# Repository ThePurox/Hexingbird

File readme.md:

# Hexingbird
Hexingbird is a [hummingbird](https://github.com/PJE66/hummingbird) style split 30 key keyboard designed around [hexagonal keycaps](https://hw.s-ol.nu/HEX-keycaps/), which require Choc v1 switches.
It uses the CH552T controller and [FAK firmware](https://github.com/semickolon/fak).

The electronic design is inspired by the [MIAO MCU board](https://github.com/kilipan/miao) and adapted for split operation.

# BOM
| Part             | LCSC-Part Nr | amount |
|------------------|--------------|--------|
| USB-C            | C223907      | 4      |
| CH552T           | C111367      | 2      |
| BAV70 Diodes     | C727123      | 18     |
| USBLC6-2SC6      | C6807798     | 2      |
| PMEG2010EA       | C193668      | 2      |
| Push buttons     | C115357      | 4      |
| Fuse             | C311055      | 2      |
| 5.1k-Resistor    | C23186       | 4      |
| 10k-Resistor     | C25804       | 2      |
| 1uF-Capacitor    | C2991434     | 4      |
| Hot-Swap-Sockets |              | 30     |
| Choc V1 Switches |              | 30     |

# Buildguide
Before we start let's get our coordinates clear.
The PCB is reversible, but not symmetric when flipped.
You can see this for example with the USB-jack; it's contacts for soldering are only on one side.
I will refer to this side as right top `RT`.
The top side of the right half (`RT`) is equivalent to the bottom side of the left half `LB`.
And vice versa the top side of the left half `LT` is equivalent to the bottom side of right half `RB`.

## Right half
Start with soldering the right half of the keyboard.
This side is easier, as all components (except for the hot-swap sockets) are soldered to the same side, i.e. `RT`.
I advise using a hotplate or hot air to solder the MCU and the USB-jack.
If you are experienced with hand soldering feel free to solder them by hand.
Three components require you to pay attention to the orientation of the component, i.e. the `CH552T`, `USBLC6-2SC6` and `PMEG2010EA`, the latter two are diodes for the ESD-protection.
For the `CH552T` and `USBLC6-2SC6` there are white lines on the PCB, with one line being slightly longer than the other. The side with the extended line is marks the corner in which the dot/dimple of the IC has to be placed.

The next components to solder are the USB-jacks.
After you have successfully soldered the electric pins of the USB-jack, make sure to also solder the metal legs on the side, as they will give stability to the jack.

Now you have completed the hard part, treat yourself with some pads on the shoulder, before we continue with the small two terminal components.
Next to the `CH552T` you will find four pads, these are for the two capacitors.
Next to the top USB-jack you see spots for four components, from top right to bottom left these are the fuse, `PMEG2010EA`-Schottky diode, and two 5.1k Resistors.
The orientation of the diode is important.
The white line on its housing has to face away from the USB-jack.
Another way of orientating the diode is to look closely on the solder-pads of the diode.
One of the pads is shaped like an arrow.
The arrow points towards the white line of the diode.
For the other components the orientation does not matter.

Next solder in the `RESET` and `BOOT` push buttons, as well as the 10k resistor between them.
Finally  install the `BAV70` diodes.

Congratulations, you have now soldered in all the necessary electronic components, you can now flash the firmware (see below) for the central half on this half and test, whether all keys work. All keys except the tucky thumb should work. The tucky thumb requires a bodge wire to function. Will we add the bodge wire, after soldering the hot-swap sockets.

The solder pads above and below the USB-jacks, as well as the pads next to the bottom USB-jack are supposed to be left empty.

## Left half
The left half is a bit more tricky to solder than the right half, as the MCU and the USB-jacks are soldered to different sides of the PCB.
If you are not careful while soldering, the components on the other side might fall off the PCB, or shift around. You don't want either to happen.
One trick to work around this annoyance, is to solder the `CH552T` and `USBLC6-2SC6` to `LT` first, then solder the USB-jacks to `LB`. When soldering the USB-jacks, only put the USB-jack part of the PCB on your hotplate.
If you heat up to much of the PCB, the MCU will fall off the board.

With the USB-jacks, the `CH552T` and the `USBLC6-2SC6` in place, you have completed the hardest part of soldering this keyboard.
From here on it is smooth sailing.
Next solder the `BAV70` diodes to `LB`.
Solder in all the remaining passive components to `LT` just as with the right half.

You can now test the left half by flashing the peripheral firmware onto it, connecting the two keyboard halves with through the USB-jacks with a bird next to them.

After you have confirmed, that all keys except for the tucky thumbs work, it is time to solder in the hot-swap sockets to the bottom sides of the two halves, i.e. the sides without the MCU.

If you are one of the lucky people that got a PCB at Mechanicon 2024 you have to add a bodge wire as shown in the picture, to each half:

# Flashing the firmware
This keyboard is designed for the [FAK-firmware](https://github.com/semickolon/fak).
I've provided some example configuration files in [my fork](https://github.com/ThePurox/fak-config) of the fak-config repository with the keyboard name `hexingbird`.

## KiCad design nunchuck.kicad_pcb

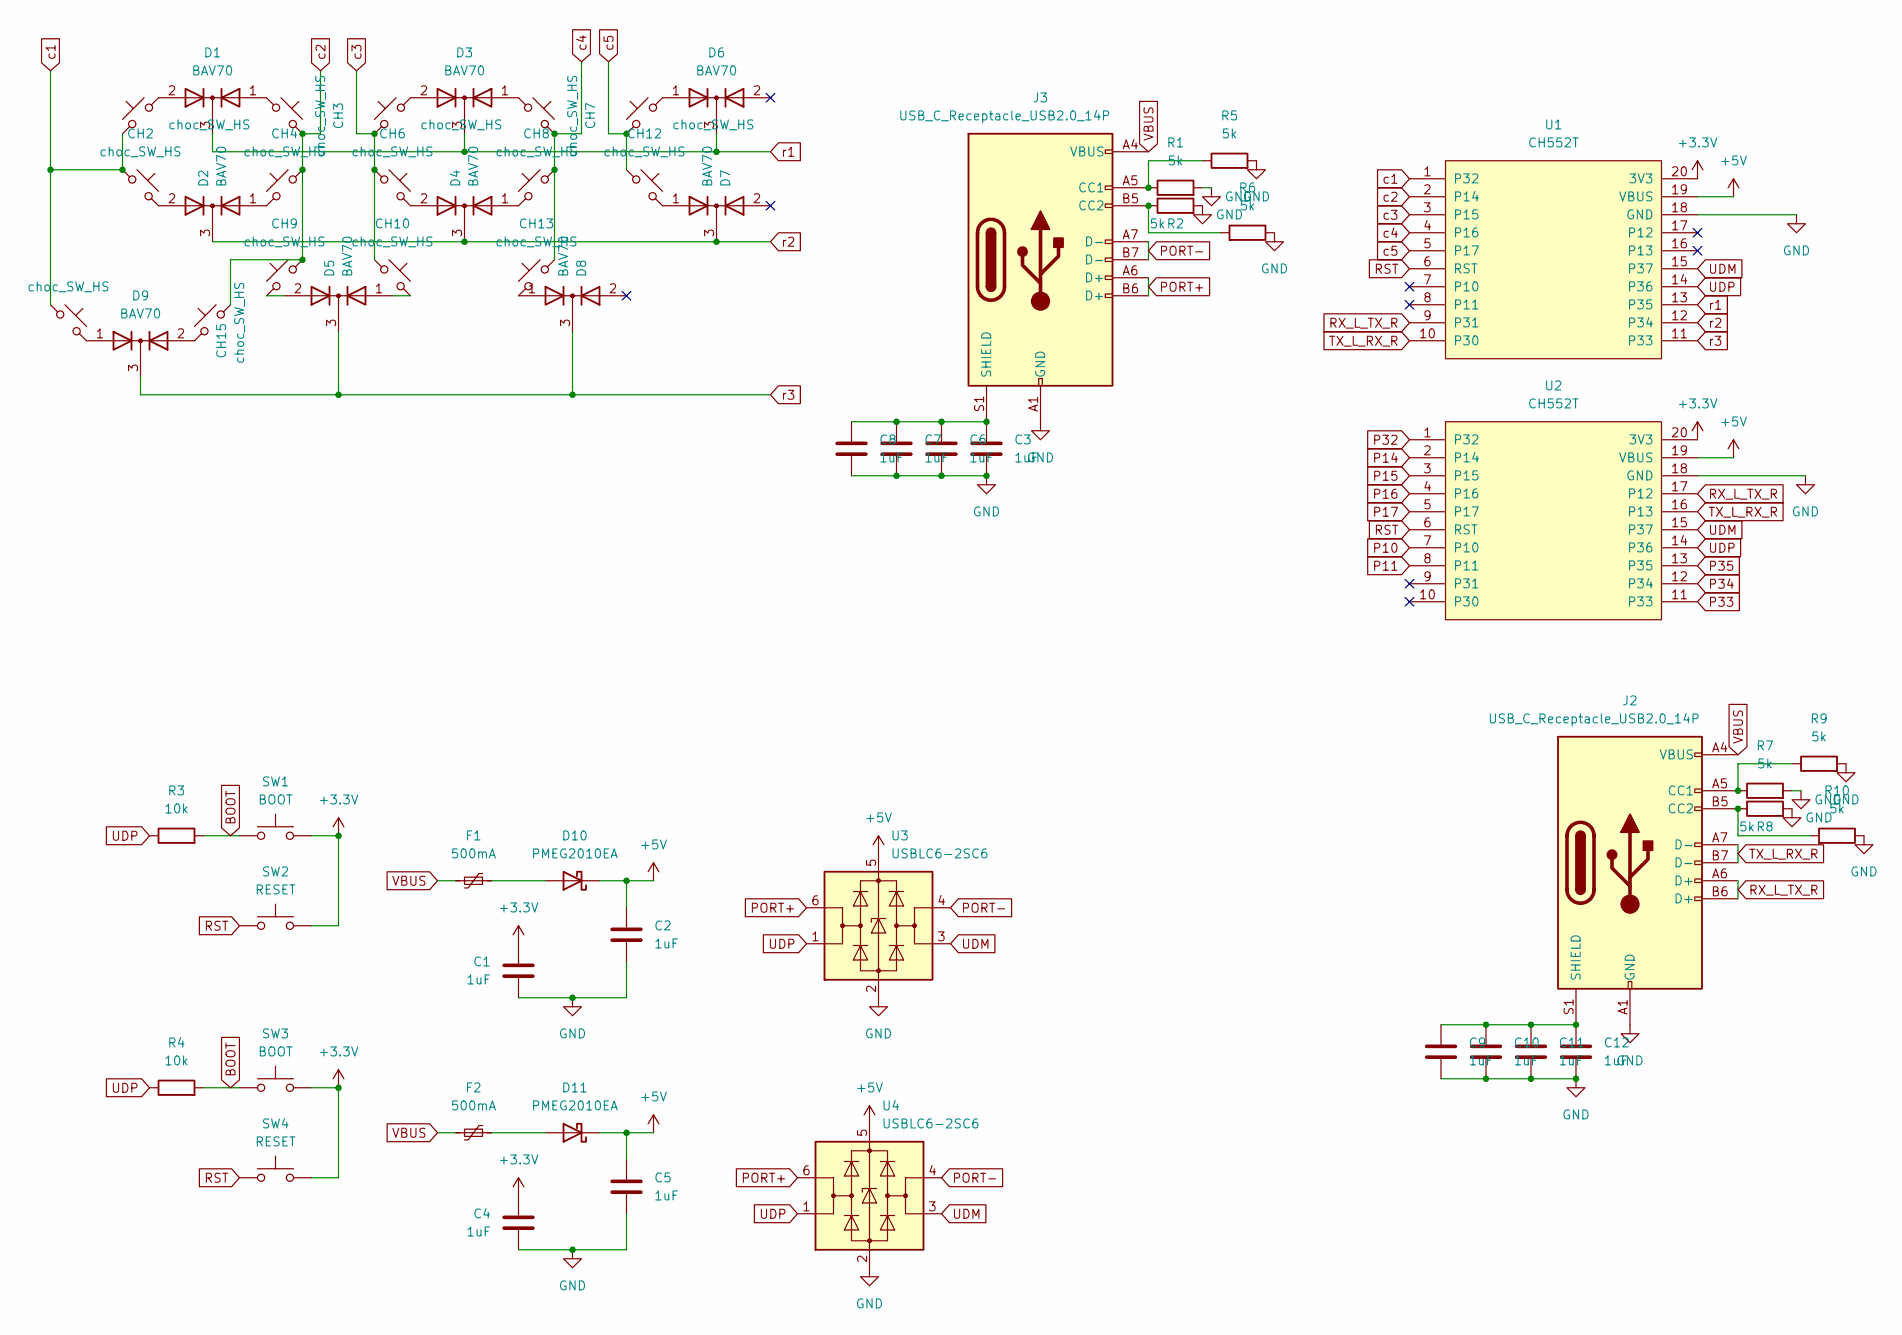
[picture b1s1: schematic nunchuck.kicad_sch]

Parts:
C1, C2, C3, C4, C5, C6, C7, C8, C9, C10, C11, C12: 1uF; C_0603_1608Metric_Pad1.08x0.95mm_HandSolder
CH1, CH2, CH3, CH4, CH5, CH6, CH7, CH8, CH9, CH10, CH11, CH12, CH13, CH14, CH15: choc_SW_HS; PG1350_hotswap_reversible
D1, D2, D3, D4, D5, D6, D7, D8, D9: BAV70; SOT-23
D10, D11: PMEG2010EA; D_SOD-323_HandSoldering
F1, F2: 500mA; Fuse_0603_1608Metric_Pad1.05x0.95mm_HandSolder
J2, J3: USB_C_Receptacle_USB2.0_14P; USB_C_Receptacle_HRO_TYPE-C-31-M-14
R1, R2, R5, R6, R7, R8, R9, R10: 5k; R_0603_1608Metric_Pad0.98x0.95mm_HandSolder
R3, R4: 10k; R_0603_1608Metric_Pad0.98x0.95mm_HandSolder
SW1, SW3: BOOT; SW_Push_SPST_NO_Alps_SKRK
SW2, SW4: RESET; SW_Push_SPST_NO_Alps_SKRK
U1, U2: CH552T; TSSOP-20_4.4x6.5mm_P0.65mm; LCSC C111367
U3, U4: USBLC6-2SC6; SOT-23-6

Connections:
+3.3V: C1.1, C4.1, SW1.2, SW2.2, SW3.2, SW4.2, U1.20 (3V3), U2.20 (3V3)
+5V: C2.1, C5.1, D10.1 (K), D11.1 (K), U1.19 (VBUS), U2.19 (VBUS), U3.5 (VBUS), U4.5 (VBUS)
BOOT: R3.2, R4.2, SW1.1, SW3.1
GND: C1.2, C2.2, C3.2, C4.2, C5.2, C6.2, C7.2, C8.2, C9.2, C10.2, C11.2, C12.2, J2.A1 (GND), J2.A12 (GND), J2.B1 (GND), J2.B12 (GND), J3.A1 (GND), J3.A12 (GND), J3.B1 (GND), J3.B12 (GND), R1.2, R2.2, R5.2, R6.1, R7.2, R8.2, R9.2, R10.1, U1.18 (GND), U2.18 (GND), U3.2 (GND), U4.2 (GND)
unnamed: CH1.2, D1.2 (A)
unnamed: CH2.2, D2.2 (A)
unnamed: CH3.2, D1.1 (A)
unnamed: CH4.2, D2.1 (A)
unnamed: CH5.2, D3.2 (A)
unnamed: CH6.2, D4.2 (A)
unnamed: CH7.2, D3.1 (A)
unnamed: CH8.2, D4.1 (A)
unnamed: CH9.2, D5.2 (A)
unnamed: CH10.2, D5.1 (A)
unnamed: CH11.2, D6.1 (A)
unnamed: CH12.2, D7.1 (A)
unnamed: CH13.2, D8.1 (A)
unnamed: CH14.2, D9.1 (A)
unnamed: CH15.2, D9.2 (A)
unnamed: D10.2 (A), F1.1
unnamed: D11.2 (A), F2.1
unnamed: J2.A5 (CC1), R7.1, R9.1
unnamed: J2.B5 (CC2), R8.1, R10.2
unnamed: C9.1, C10.1, C11.1, C12.1, J2.S1 (SHIELD)
unnamed: J3.A5 (CC1), R1.1, R5.1
unnamed: J3.B5 (CC2), R2.1, R6.2
unnamed: C3.1, C6.1, C7.1, C8.1, J3.S1 (SHIELD)
P10: U2.7 (P10)
P11: U2.8 (P11)
P14: U2.2 (P14)
P15: U2.3 (P15)
P16: U2.4 (P16)
P17: U2.5 (P17)
P32: U2.1 (P32)
P33: U2.11 (P33)
P34: U2.12 (P34)
P35: U2.13 (P35)
PORT+: J3.A6 (D+), J3.B6 (D+), U3.6 (I/O1), U4.6 (I/O1)
PORT-: J3.A7 (D-), J3.B7 (D-), U3.4 (I/O2), U4.4 (I/O2)
RST: SW2.1, SW4.1, U1.6 (RST), U2.6 (RST)
RX_L_TX_R: J2.A6 (D+), J2.B6 (D+), U1.9 (P31), U2.17 (P12)
TX_L_RX_R: J2.A7 (D-), J2.B7 (D-), U1.10 (P30), U2.16 (P13)
UDM: U1.15 (P37), U2.15 (P37), U3.3 (I/O2), U4.3 (I/O2)
UDP: R3.1, R4.1, U1.14 (P36), U2.14 (P36), U3.1 (I/O1), U4.1 (I/O1)
VBUS: F1.2, F2.2, J2.A4 (VBUS), J2.A9 (VBUS), J2.B4 (VBUS), J2.B9 (VBUS), J3.A4 (VBUS), J3.A9 (VBUS), J3.B4 (VBUS), J3.B9 (VBUS)
c1: CH1.1, CH2.1, CH14.1, U1.1 (P32)
c2: CH3.1, CH4.1, CH9.1, CH15.1, U1.2 (P14)
c3: CH5.1, CH6.1, CH10.1, U1.3 (P15)
c4: CH7.1, CH8.1, CH13.1, U1.4 (P16)
c5: CH11.1, CH12.1, U1.5 (P17)
r1: D1.3 (K), D3.3 (K), D6.3 (K), U1.13 (P35)
r2: D2.3 (K), D4.3 (K), D7.3 (K), U1.12 (P34)
r3: D5.3 (K), D8.3 (K), D9.3 (K), U1.11 (P33)

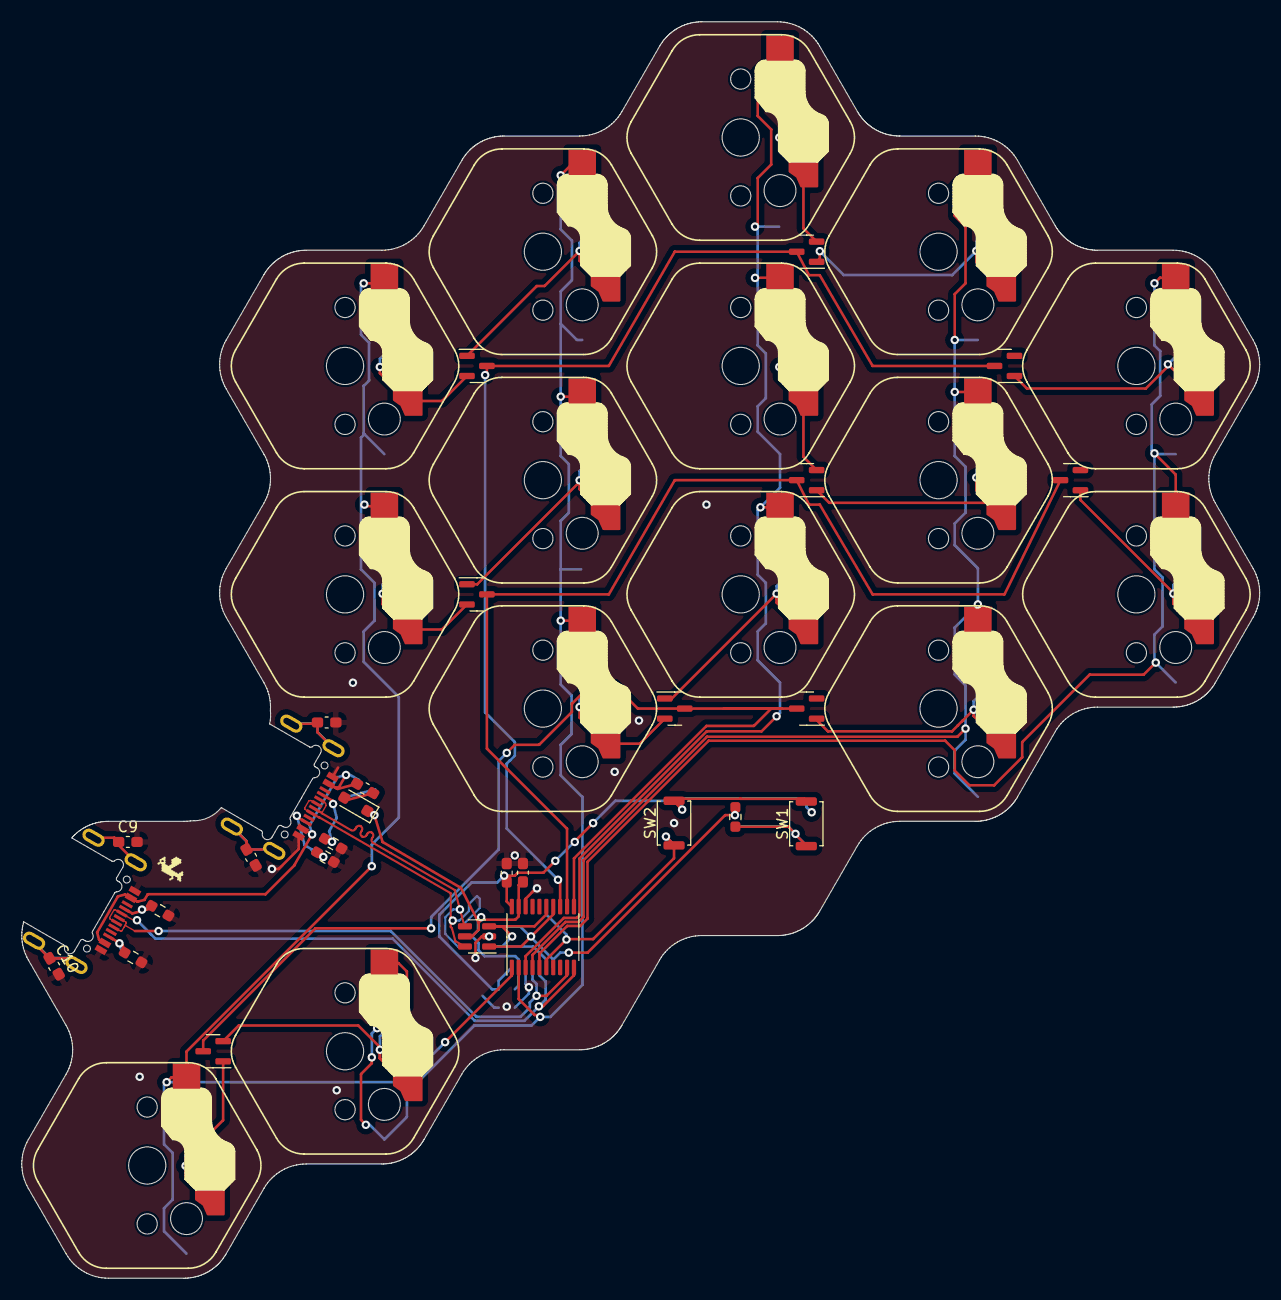
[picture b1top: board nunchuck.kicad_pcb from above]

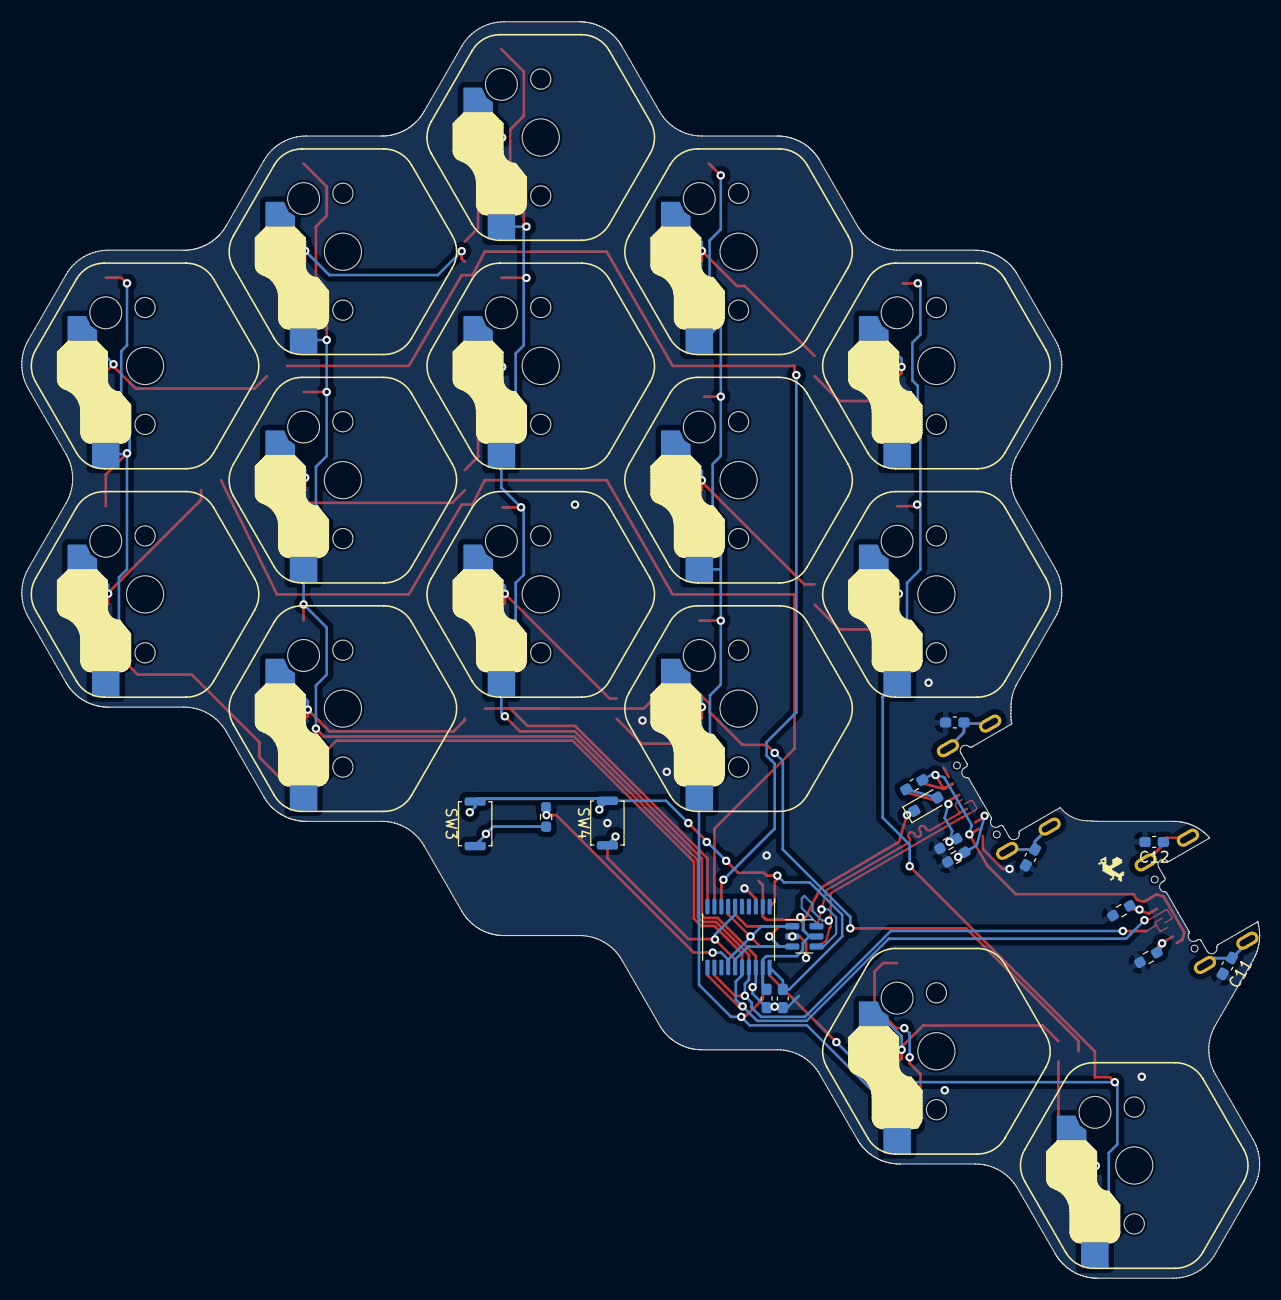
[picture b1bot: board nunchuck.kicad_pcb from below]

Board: 2 copper layers, 116.5 x 118.2 mm, 60 parts (17 on the bottom side), 43 nets.

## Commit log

2024-03-08 init
2024-03-18 before hexing
2024-03-19 hexed-ground
2024-04-12 added missing connections on back side
2024-05-19 corrected wrongly connected thumb key, and removed unnecessary 5k resistors
2024-06-04 added readme
2024-06-23 added buildguide
2024-06-23 embedded bodge wire
2024-06-23 added reference to flashing
